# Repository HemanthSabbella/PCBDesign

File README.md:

# Hardware designs

- **EMI_sensing_board:** Design and Fabrication of EMI sensing board using a current transformer with a
low noise amplifier.
- **Constant Current LED Driver Board:** Design and Fabrication of constant current LED board for testing
portable spectrometer.
- **IIITDuino:** Design of in-home version of Arduino for IIIT-D.
- **Breakout Boards and custom made libraries:** Mux - ADG736, ADG719, LEDs - 1316, L424, LHT674,
OSI-330 series, VSMB2020.

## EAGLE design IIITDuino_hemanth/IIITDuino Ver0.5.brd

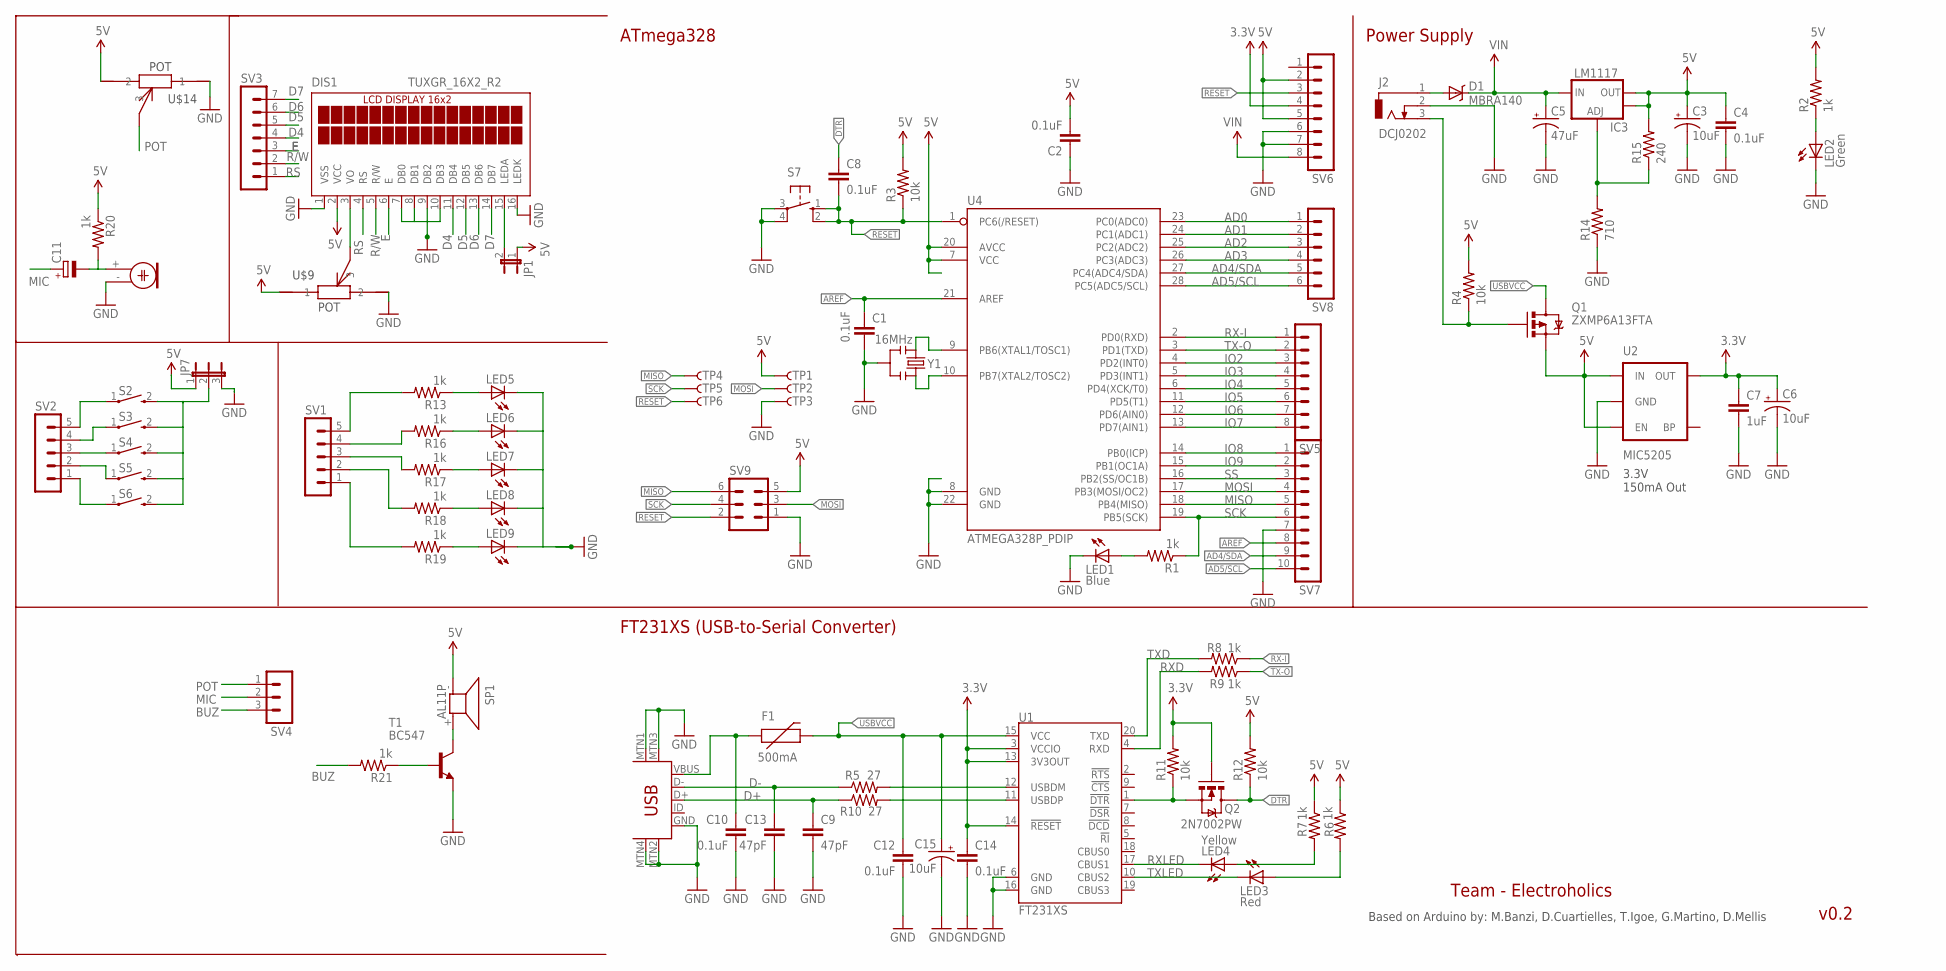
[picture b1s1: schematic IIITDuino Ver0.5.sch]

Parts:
C1, C2, C4, C8, C10, C12, C14: 0.1uF; 0603-CAP
C3, C6, C15: 10uF; EIA3216
C5: 47uF; PANASONIC_D
C7: 1uF; 0603-CAP
C9, C13: 47pF; 0603-CAP
C11: CPOL-EUE2.5-5; E2,5-5
D1: MBRA140; SMA-DIODE
DIS1: TUXGR_16X2_R2; LCD_16X2_PAC
F1: 500mA; PTC-1206
IC3: LM1117; SOT223-ALT1
J2: DCJ0202
JP1: JP1E; JP1
JP7: JP2E; JP2
LED1: Blue; LED-1206-NO_SILK
LED2: Green; LED-1206-NO_SILK
LED3: Red; LED-1206-NO_SILK
LED4: Yellow; LED-1206-NO_SILK
LED5, LED6, LED7, LED8, LED9: LEDCHIP-LED0805; CHIP-LED0805
M1: ELECTRET_MICROPHON-TOM-1545P-R; TOM-1545P-R
Q1: ZXMP6A13FTA; SOT23-3
Q2: 2N7002PW; SOT323
R1, R2, R6, R7, R8, R9, R13, R16, R17, R18, R19, R20, R21: 1k; 0603-RES
R3, R4, R11, R12: 10k; 0603-RES
R5, R10: 27; 0603-RES
R14: 710; 0603-RES
R15: 240; 0603-RES
S2, S3, S4, S5, S6, S7: 10-XX; B3F-10XX
SP1: AL11P
SV1, SV2: MA05-1
SV3: MA07-1
SV4: MA03-1
SV5, SV6: MA08-1
SV7: MA10-1
SV8: MA06-1
SV9: MA03-2
T1: BC547; TO92
TP1, TP2, TP3, TP4, TP5, TP6: TP-3x5; PAD.03X.05
U1: FT231XS; SSOP20_L
U2: MIC5205; SOT23-5
U4: ATMEGA328P_PDIP; DIL28-3
U$9, U$14: POT; CA9V
U$13: USB-MINIB-5PIN; USB-MINIB
Y1: 16MHz; RESONATOR-SMD

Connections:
3.3V: C6.A (+), C7.1, C14.1, Q2.1 (G), R11.2, SV6.4, U1.3 (VCCIO), U1.13 (3V3OUT), U1.14 (!RESET), U2.5 (OUT)
5V: C2.2, C3.A (+), C4.1, DIS1.2 (VCC), IC3.2 (OUT), IC3.4 (OUT), JP1.1, Q1.2 (S), R2.2, R3.2, R4.2, R6.1, R7.1, R12.2, R15.2, R20.1, SP1.- (1), SV6.2, SV6.5, SV9.5, TP1.P$1, U2.1 (IN), U2.3 (EN), U4.7 (VCC), U4.20 (AVCC), U$9.A (1), U$14.K (2)
AD0: SV8.1, U4.23 (PC0(ADC0))
AD1: SV8.2, U4.24 (PC1(ADC1))
AD2: SV8.3, U4.25 (PC2(ADC2))
AD3: SV8.4, U4.26 (PC3(ADC3))
AD4/SDA: SV7.9, SV8.5, U4.27 (PC4(ADC4/SDA))
AD5/SCL: SV7.10, SV8.6, U4.28 (PC5(ADC5/SCL))
AREF: C1.1, SV7.8, U4.21 (AREF)
BUZ: R21.2, SV4.3
D4: DIS1.11 (DB4), SV3.4
D5: DIS1.12 (DB5), SV3.5
D6: DIS1.13 (DB6), SV3.6
D7: DIS1.14 (DB7), SV3.7
D+: C9.1, R10.1, U$13.D+
D-: C13.1, R5.1, U$13.D-
DTR: C8.1, Q2.3 (D), R12.1
E: DIS1.6 (E), SV3.3
GND: C1.2, C2.1, C3.C (-), C4.2, C5.-, C6.C (-), C7.2, C9.2, C10.2, C12.2, C13.2, C14.2, C15.C (-), DIS1.1 (VSS), DIS1.7 (DB0), DIS1.8 (DB1), DIS1.9 (DB2), DIS1.10 (DB3), DIS1.16 (LEDK), J2.2, LED1.C, LED2.C, LED5.C, LED6.C, LED7.C, LED8.C, LED9.C, M1.- (2), R14.1, S7.3, S7.4 (P1), SV6.6, SV6.7, SV7.7, SV9.1, T1.1 (E), TP3.P$1, U1.6 (GND), U1.16 (GND), U2.2 (GND), U4.8 (GND), U4.22 (GND), U$9.K (2), U$13.GND, U$13.MTN1 (MTN2), U$13.MTN2 (MTN3), U$13.MTN3 (MTN1), U$13.MTN4, U$14.A (1), Y1.2
INSERT: J2.3, Q1.1 (G), R4.1
IO2: SV5.3, U4.4 (PD2(INT0))
IO3: SV5.4, U4.5 (PD3(INT1))
IO4: SV5.5, U4.6 (PD4(XCK/T0))
IO5: SV5.6, U4.11 (PD5(T1))
IO6: SV5.7, U4.12 (PD6(AIN0))
IO7: SV5.8, U4.13 (PD7(AIN1))
IO8: SV7.1, U4.14 (PB0(ICP))
IO9: SV7.2, U4.15 (PB1(OC1A))
MIC: C11.+, SV4.2
MISO: SV7.5, SV9.6, TP4.P$1, U4.18 (PB4(MISO))
MOSI: SV7.4, SV9.3, TP2.P$1, U4.17 (PB3(MOSI/OC2))
unnamed: LED1.A, R1.2
unnamed: LED2.A, R2.1
unnamed: U4.9 (PB6(XTAL1/TOSC1)), Y1.1
unnamed: U4.10 (PB7(XTAL2/TOSC2)), Y1.3
unnamed: DIS1.3 (VO), U$9.S (3)
unnamed: R5.2, U1.12 (USBDM)
unnamed: R10.2, U1.11 (USBDP)
unnamed: LED3.A, R6.2
unnamed: LED4.A, R7.2
unnamed: Q2.2 (S), R11.1, U1.1 (!DTR)
unnamed: IC3.1 (ADJ), R14.2, R15.1
unnamed: DIS1.15 (LEDA), JP1.2
unnamed: S2.1, SV2.5
unnamed: LED5.A, R13.1
unnamed: LED6.A, R16.1
unnamed: LED7.A, R17.1
unnamed: LED8.A, R18.1
unnamed: LED9.A, R19.1
unnamed: R13.2, SV1.5
unnamed: R16.2, SV1.4
unnamed: R17.2, SV1.3
unnamed: R18.2, SV1.2
unnamed: R19.2, SV1.1
unnamed: S3.1, SV2.4
unnamed: S4.1, SV2.3
unnamed: S5.1, SV2.2
unnamed: S6.1, SV2.1
unnamed: JP7.2, S2.2 (S), S3.2 (S), S4.2 (S), S5.2 (S), S6.2 (S)
unnamed: SP1.+ (2), T1.3 (C)
unnamed: C11.-, M1.+ (1), R20.2
unnamed: R21.1, T1.2 (B)
POT: SV4.1, U$14.S (3)
PWRIN: D1.A, J2.1
R/W: DIS1.5 (R/W), SV3.2
RESET: C8.2, R3.1, S7.1 (S), S7.2 (S1), SV6.3, SV9.2, TP6.P$1, U4.1 (PC6(/RESET))
RS: DIS1.4 (RS), SV3.1
RX-I: R8.1, SV5.1, U4.2 (PD0(RXD))
RXD: R9.2, U1.4 (RXD)
RXLED: LED4.C, U1.17 (CBUS1)
SCK: R1.1, SV7.6, SV9.4, TP5.P$1, U4.19 (PB5(SCK))
SS: SV7.3, U4.16 (PB2(SS/OC1B))
TX-O: R9.1, SV5.2, U4.3 (PD1(TXD))
TXD: R8.2, U1.20 (TXD)
TXLED: LED3.C, U1.10 (CBUS2)
USBVCC: C12.1, C15.A (+), F1.2, Q1.3 (D), U1.15 (VCC)
VIN: C5.+, D1.C, IC3.3 (IN), SV6.8
VUSB: C10.1, F1.1, U$13.VBUS

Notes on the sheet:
Power Supply
ATmega328
FT231XS (USB-to-Serial Converter)
Based on Arduino by: M.Banzi, D.Cuartielles, T.Igoe, G.Martino, D.Mellis
3.3V 150mA Out
Team - Electroholics
v0.2

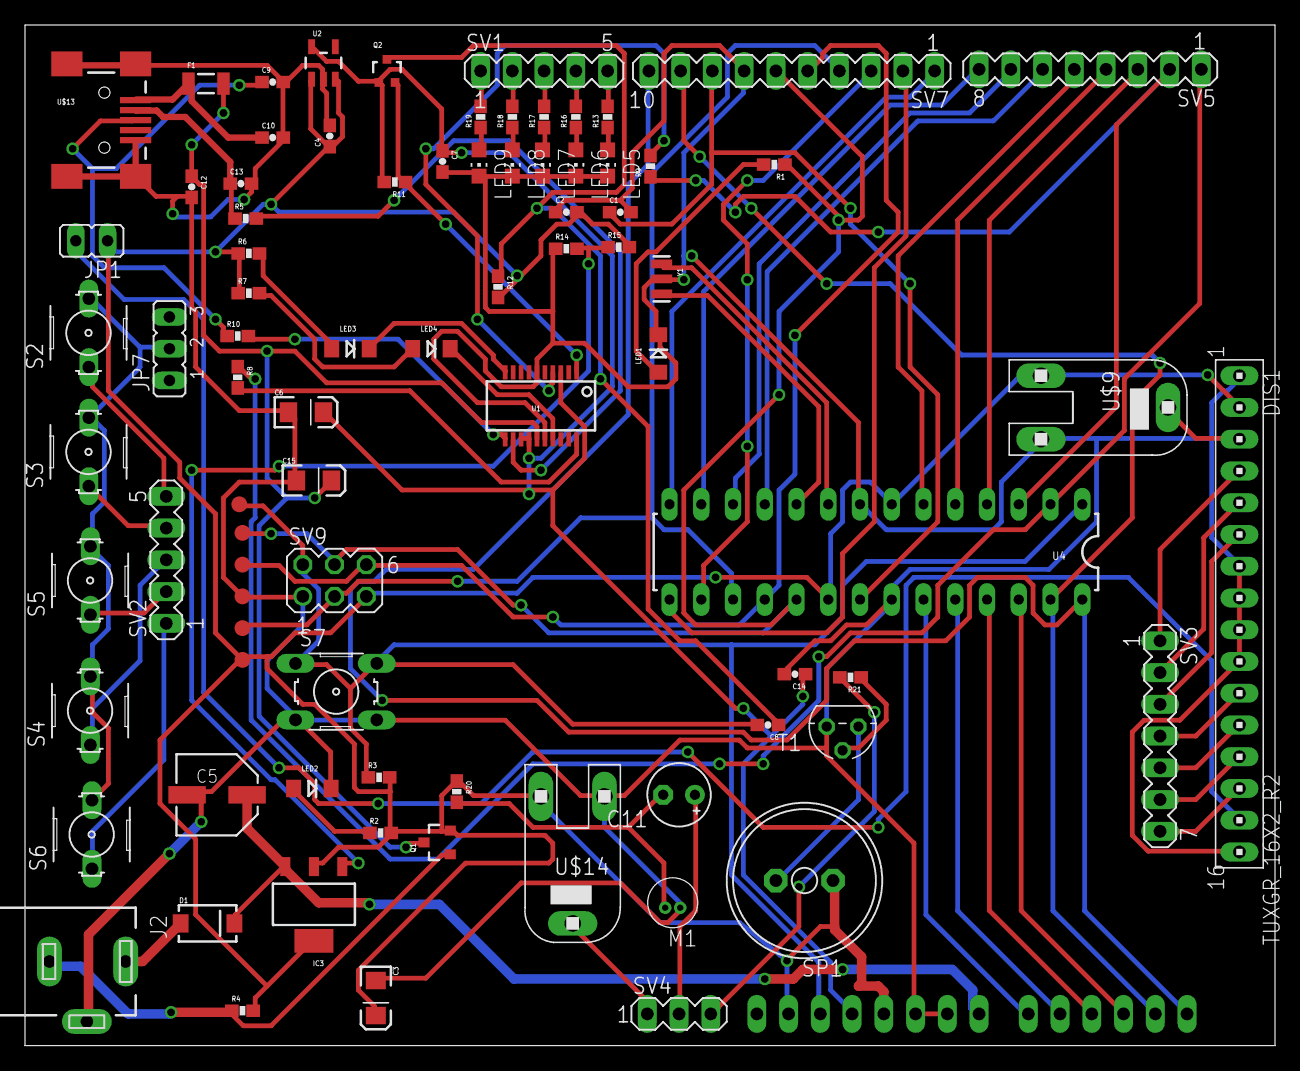
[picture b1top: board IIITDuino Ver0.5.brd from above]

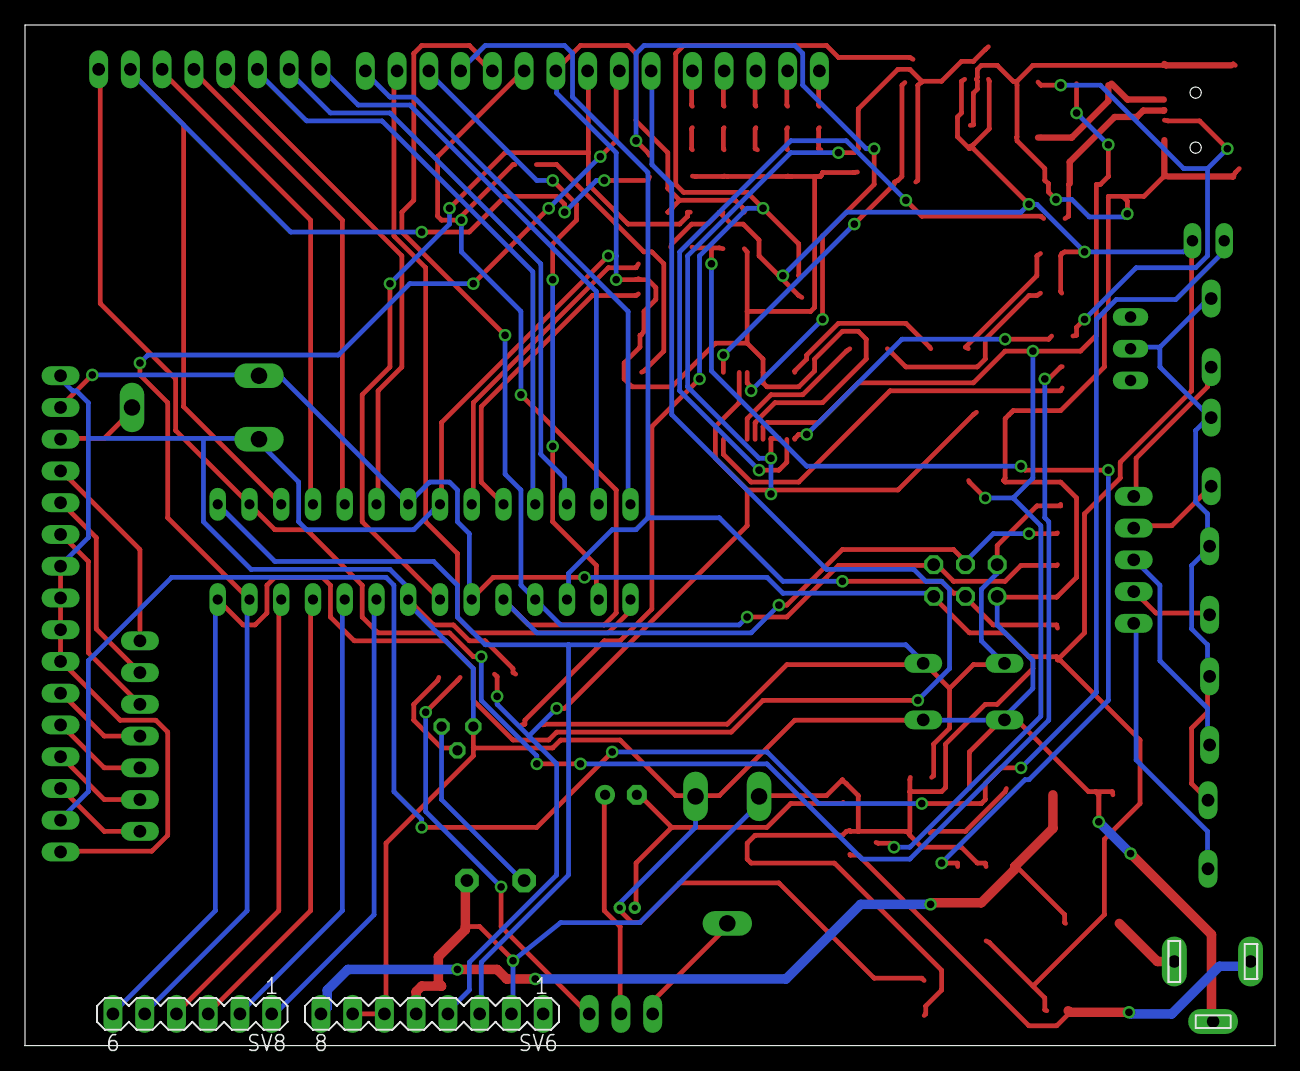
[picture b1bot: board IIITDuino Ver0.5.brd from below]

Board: 2 copper layers, 99.9 x 81.5 mm, 85 parts (2 on the bottom side), 78 nets.

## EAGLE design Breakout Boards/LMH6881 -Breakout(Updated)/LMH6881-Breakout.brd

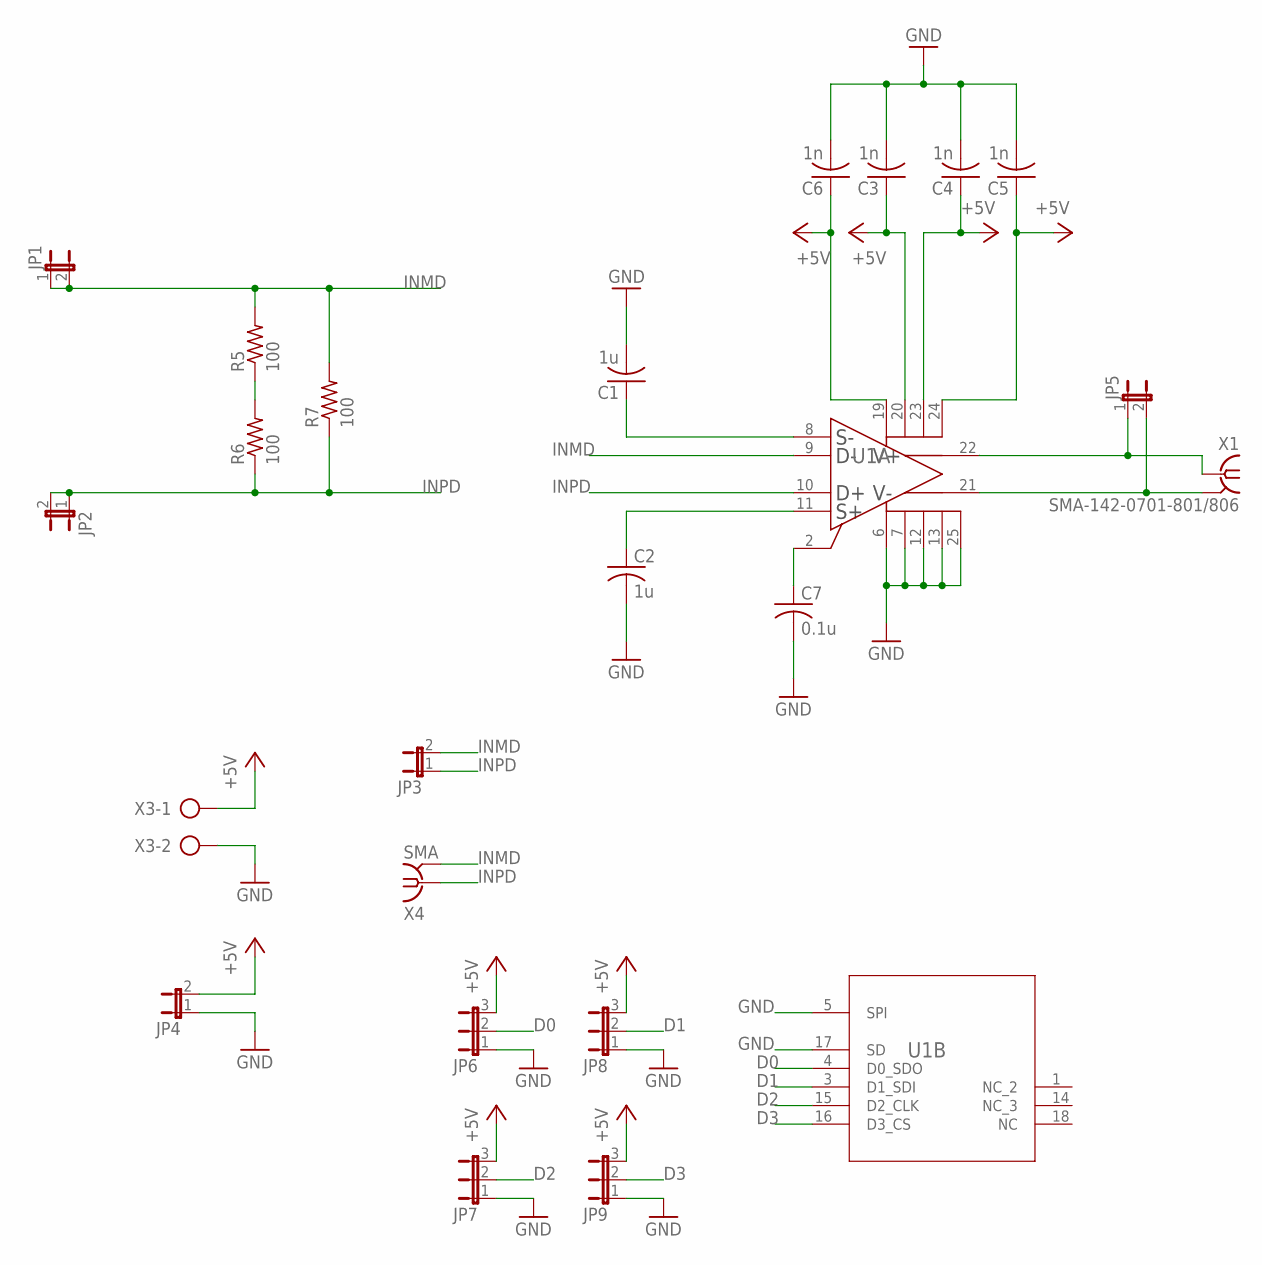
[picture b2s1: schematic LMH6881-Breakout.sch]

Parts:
C1, C2: 1u; C0805
C3, C4, C5, C6: 1n; C0805
C7: 0.1u; C0805
JP1, JP2, JP3, JP4, JP5: JP1E; JP1
JP6, JP7, JP8, JP9: JP2E; JP2
R5, R6, R7: 100; R0805
U1: LMH6881SQX/NOPB; RTW0024A
X1: SMA-142-0701-801/806; J502-ND-142-0701-801/806
X3: AK500/2
X4: SMA; J502-ND-142-0701-801/806

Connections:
+5V: C3.1, C4.1, C5.1, C6.1, JP4.2, JP6.3, JP7.3, JP8.3, JP9.3, U1.19 (VCC_2), U1.20 (VCC_3), U1.23 (VCC_4), U1.24 (VCC), X3.1
D0: JP6.2, U1.4 (D0_SDO)
D1: JP8.2, U1.3 (D1_SDI)
D2: JP7.2, U1.15 (D2_CLK)
D3: JP9.2, U1.16 (D3_CS)
GND: C1.2, C2.2, C3.2, C4.2, C5.2, C6.2, C7.2, JP4.1, JP6.1, JP7.1, JP8.1, JP9.1, U1.5 (SPI), U1.6 (GND_2), U1.7 (GND_3), U1.12 (GND_4), U1.13 (GND), U1.17 (SD), U1.25 (PAD), X3.2
INMD: JP1.1, JP1.2, JP3.2, R5.2, R7.2, U1.9 (INMD), X4.G@1 (2), X4.G@2 (2), X4.G@3 (2), X4.G@4 (2)
INPD: JP2.1, JP2.2, JP3.1, R6.1, R7.1, U1.10 (INPD), X4.1
unnamed: C7.1, U1.2 (OCM)
unnamed: C1.1, U1.8 (INMS)
unnamed: C2.1, U1.11 (INPS)
unnamed: JP5.1, U1.22 (OUTP), X1.1
unnamed: JP5.2, U1.21 (OUTM), X1.G@1 (2), X1.G@2 (2), X1.G@3 (2), X1.G@4 (2)
unnamed: R5.1, R6.2

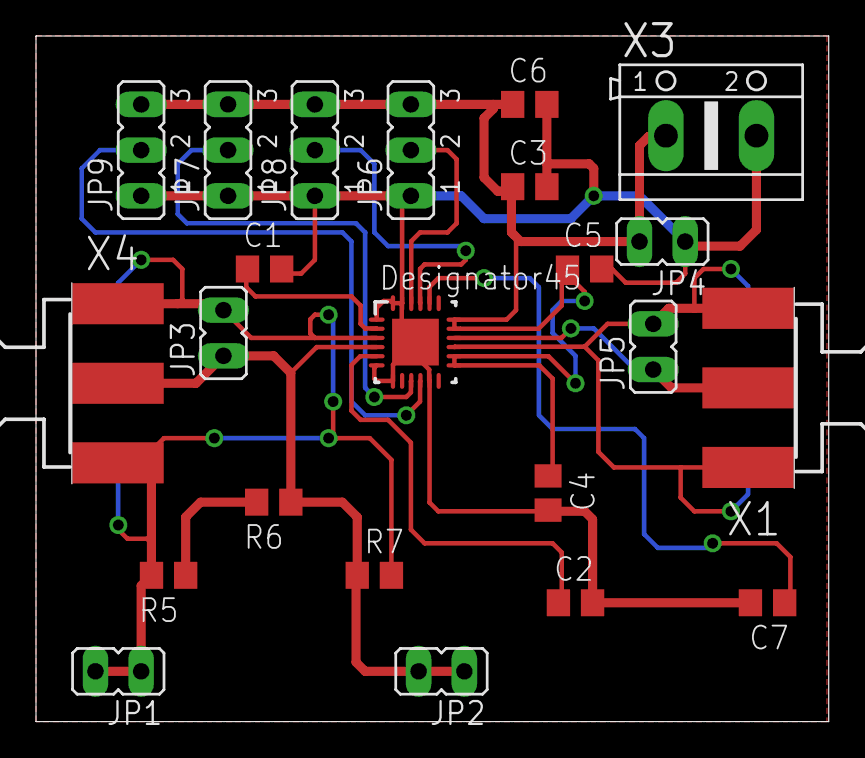
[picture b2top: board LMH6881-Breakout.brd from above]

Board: 2 copper layers, 44.0 x 38.1 mm, 23 parts (0 on the bottom side), 14 nets.

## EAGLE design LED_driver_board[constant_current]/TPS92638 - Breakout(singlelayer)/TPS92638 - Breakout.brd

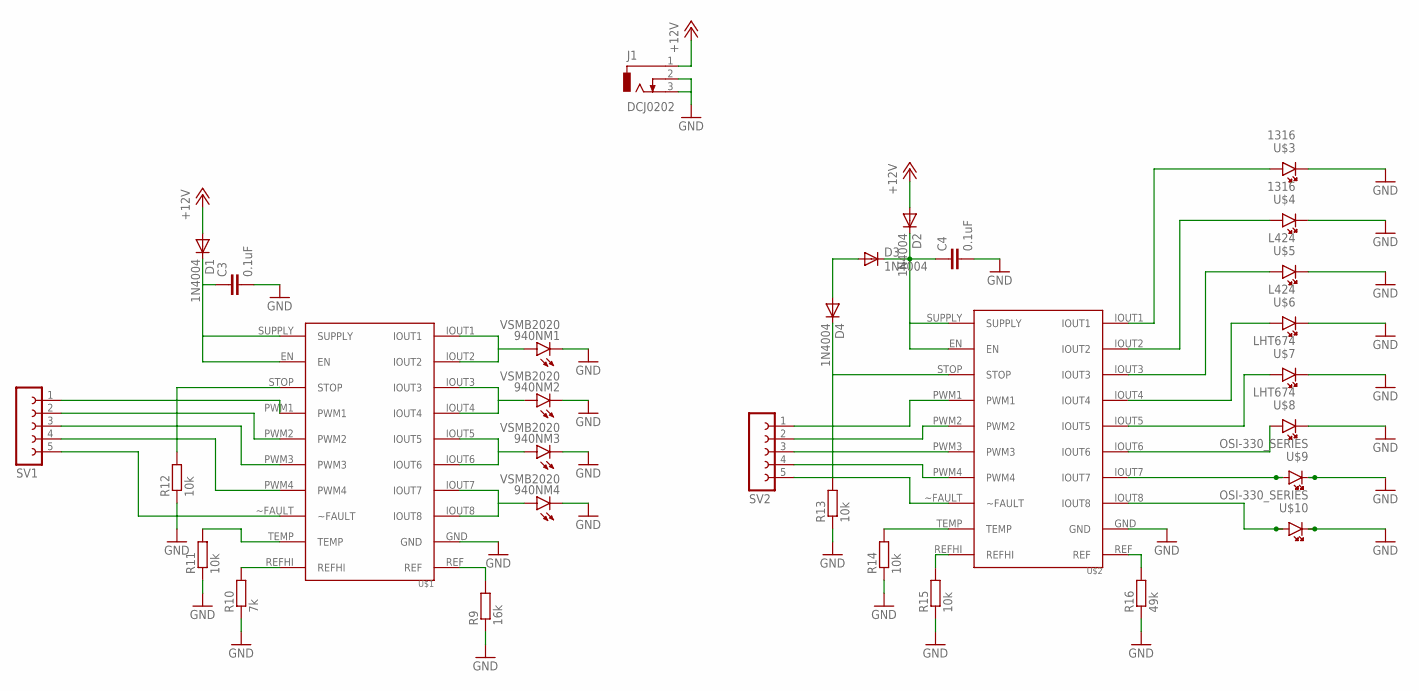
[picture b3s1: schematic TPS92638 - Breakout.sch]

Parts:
940NM1, 940NM2, 940NM3, 940NM4: VSMB2020; GULLWING-2.3MM
C3, C4: 0.1uF; C025-024X044
D1, D2, D3, D4: 1N4004; DO41-10
J1: DCJ0202
R9: 16k; 0204/7
R10: 7k; 0204/7
R11, R12, R13, R14, R15: 10k; 0204/7
R16: 49k; 0204/7
SV1, SV2: FE05-1
U$1, U$2: TPS92638
U$3, U$4: 1316
U$5, U$6: L424
U$7, U$8: LHT674
U$9, U$10: OSI-330_SERIES

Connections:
+12V: D1.A, D2.A, J1.1
GND: 940NM1.P$2 (C), 940NM2.P$2 (C), 940NM3.P$2 (C), 940NM4.P$2 (C), C3.2, C4.2, J1.2, J1.3, R9.1, R10.1, R11.1, R12.1, R13.1, R14.1, R15.1, R16.1, U$1.GND, U$2.GND, U$3.CATHODE, U$4.CATHODE, U$5.CATHODE, U$6.CATHODE, U$7.CATHODE, U$8.CATHODE, U$9.CATHODE, U$10.CATHODE
unnamed: SV1.1, U$1.PWM1
unnamed: SV1.2, U$1.PWM2
unnamed: SV1.3, U$1.PWM3
unnamed: SV1.4, U$1.PWM4
unnamed: R12.2, U$1.STOP
unnamed: SV2.1, U$2.PWM1
unnamed: SV2.2, U$2.PWM2
unnamed: SV2.3, U$2.PWM3
unnamed: SV2.4, U$2.PWM4
unnamed: D4.C, R13.2, U$2.STOP
unnamed: R10.2, U$1.REFHI
unnamed: R11.2, U$1.TEMP
unnamed: R9.2, U$1.REF
unnamed: R14.2, U$2.TEMP
unnamed: R15.2, U$2.REFHI
unnamed: R16.2, U$2.REF
unnamed: C3.1, D1.C, U$1.EN, U$1.SUPPLY
unnamed: C4.1, D2.C, D3.C, U$2.EN, U$2.SUPPLY
unnamed: 940NM1.P$1 (A), U$1.IOUT1, U$1.IOUT2
unnamed: 940NM2.P$1 (A), U$1.IOUT3, U$1.IOUT4
unnamed: U$2.IOUT1, U$3.ANODE
unnamed: 940NM3.P$1 (A), U$1.IOUT5, U$1.IOUT6
unnamed: 940NM4.P$1 (A), U$1.IOUT7, U$1.IOUT8
unnamed: U$2.IOUT2, U$4.ANODE
unnamed: U$2.IOUT3, U$5.ANODE
unnamed: U$2.IOUT4, U$6.ANODE
unnamed: U$2.IOUT5, U$7.ANODE
unnamed: U$2.IOUT6, U$8.ANODE
unnamed: U$2.IOUT7, U$9.ANODE
unnamed: U$2.IOUT8, U$10.ANODE
unnamed: SV1.5, U$1.~FAULT
unnamed: SV2.5, U$2.~FAULT
unnamed: D3.A, D4.A

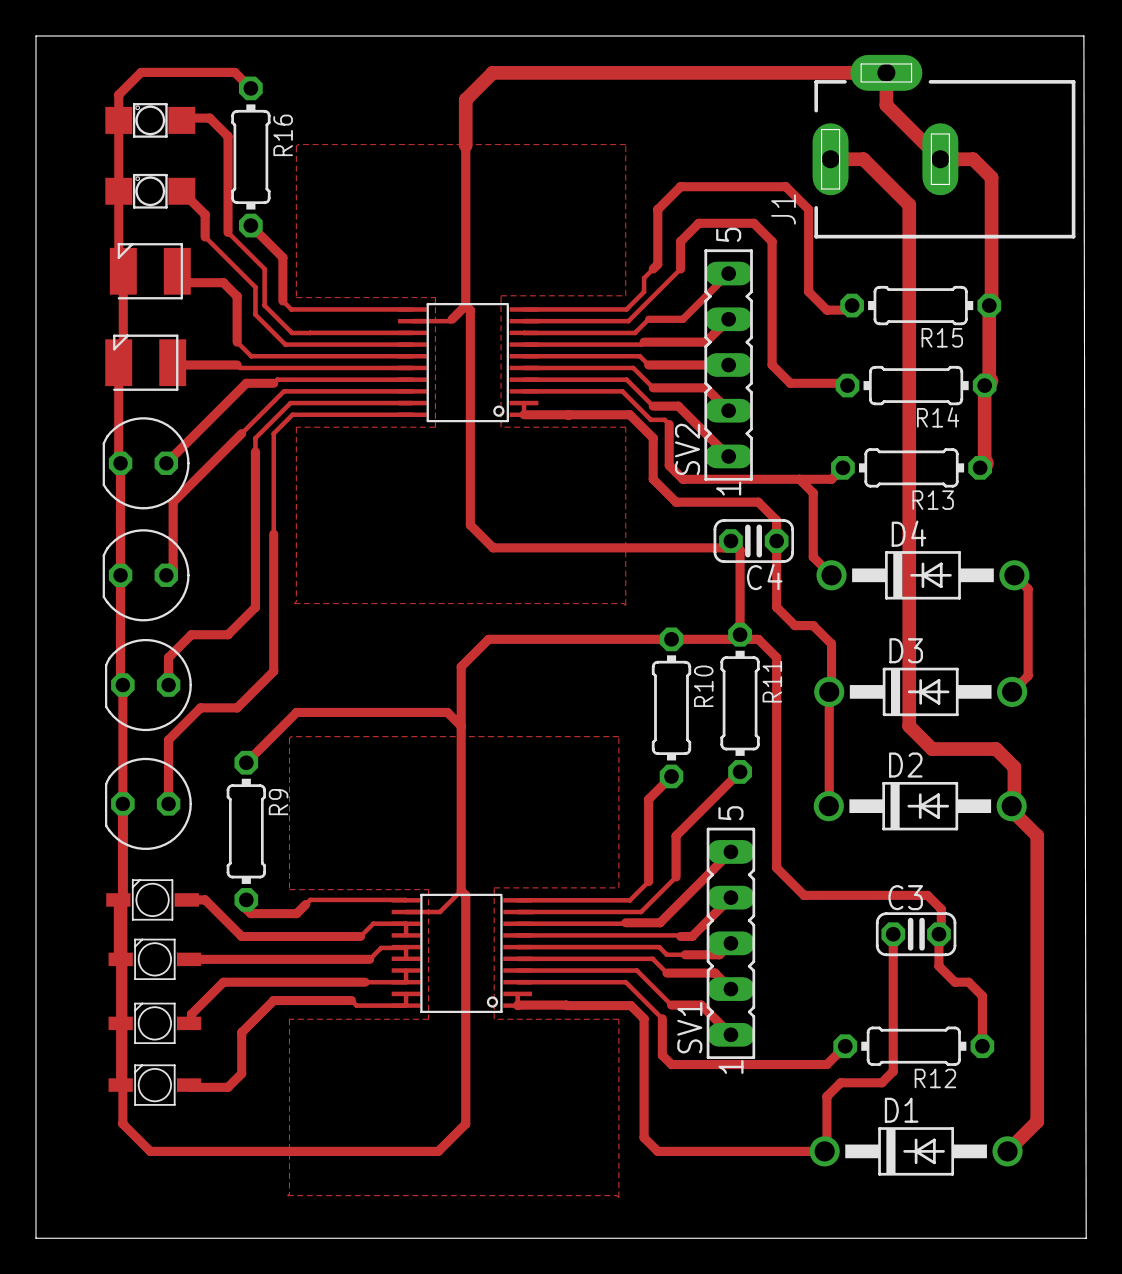
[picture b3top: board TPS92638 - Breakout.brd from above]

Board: 2 copper layers, 58.3 x 66.8 mm, 31 parts (0 on the bottom side), 35 nets.

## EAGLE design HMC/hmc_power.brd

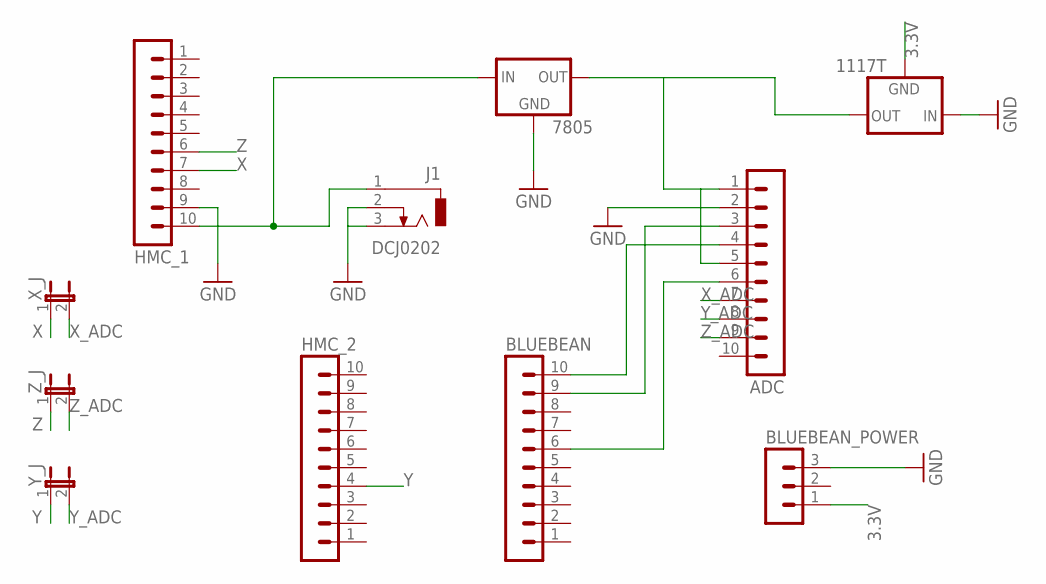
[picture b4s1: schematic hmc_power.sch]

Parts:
1117T, 7805: 78XXL
ADC: MA10-1
BLUEBEAN: MA10-1
BLUEBEAN_POWER: MA03-1
HMC_1, HMC_2: MA10-1
J1: DCJ0202
X_J: JP1E; JP1
Y_J: JP1E; JP1
Z_J: JP1E; JP1

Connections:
3.3V: 1117T.GND, BLUEBEAN_POWER.1
A1: 7805.IN, HMC_1.10, J1.1
GND: 1117T.IN, 7805.GND, ADC.2, BLUEBEAN_POWER.3, HMC_1.9, J1.2, J1.3
unnamed: 1117T.OUT, 7805.OUT, ADC.1, ADC.5
unnamed: ADC.3, BLUEBEAN.9
unnamed: ADC.4, BLUEBEAN.10
unnamed: ADC.6, BLUEBEAN.6
X: HMC_1.7, X_J.1
X_ADC: ADC.7, X_J.2
Y: HMC_2.4, Y_J.1
Y_ADC: ADC.8, Y_J.2
Z: HMC_1.6, Z_J.1
Z_ADC: ADC.9, Z_J.2

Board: 2 copper layers, 11 parts (0 on the bottom side), 13 nets, no tracks yet.

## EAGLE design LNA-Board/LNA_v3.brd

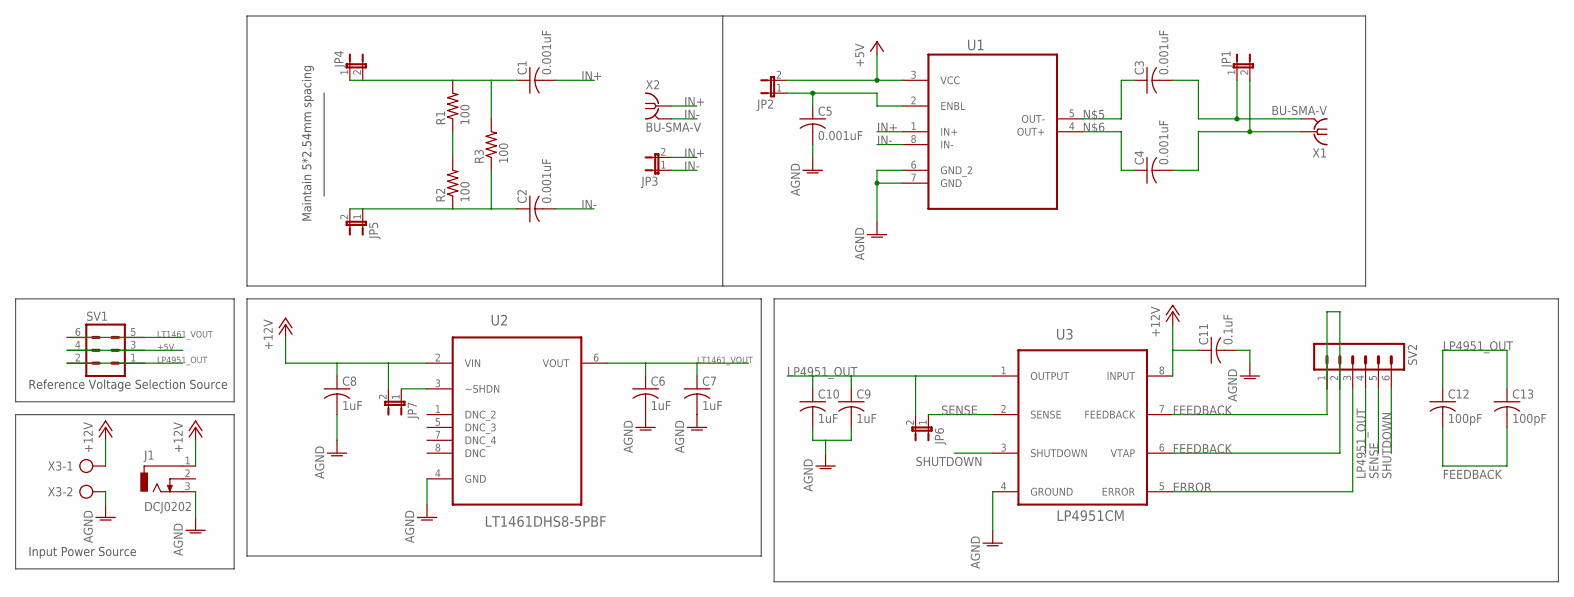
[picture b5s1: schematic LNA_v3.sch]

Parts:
C1, C2, C3, C4, C5: 0.001uF; C0805
C6, C7, C8, C9, C10: 1uF; C0805
C11: 0.1uF; C0805
C12, C13: 100pF; C0805
J1: DCJ0202
JP1, JP2, JP3, JP4, JP5, JP6, JP7: JP1E; JP1
R1, R2, R3: 100; R0805
SV1: MA03-2
SV2: MA06-1
U1: AD8350ARMZ20; SOP65P490X110-8N
U2: LT1461DHS8-5PBF; SOIC127P600X175-8N
U3: LP4951CM; SOIC127P600X175-8N
X1, X2: BU-SMA-V
X3: AK500/2

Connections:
+5V: JP2.2, SV1.3, SV1.4, U1.3 (VCC)
+12V: C8.1, C11.1, J1.1, JP7.2, U2.2 (VIN), U3.8 (INPUT), X3.1
AGND: C5.2, C6.2, C7.2, C8.2, C9.2, C10.2, C11.2, J1.3, U1.6 (GND_2), U1.7 (GND), U2.4 (GND), U3.4 (GROUND), X3.2
ERROR: SV2.3, U3.5 (ERROR)
FEEDBACK: C12.2, C13.2, SV2.1, SV2.2, U3.6 (VTAP), U3.7 (FEEDBACK)
IN+: C1.2, JP3.2, U1.1 (IN+), X2.1
IN-: C2.2, JP3.1, U1.8 (IN-), X2.2, X2.3 (2), X2.4 (2), X2.5 (2)
LP4951_OUT: C9.1, C10.1, C12.1, C13.1, JP6.2, SV1.1, SV1.2, SV2.4, U3.1 (OUTPUT)
LT1461_VOUT: C6.1, C7.1, SV1.5, SV1.6, U2.6 (VOUT)
unnamed: C1.1, JP4.1, JP4.2, R1.2, R3.2
unnamed: R1.1, R2.2
unnamed: C5.1, JP2.1, U1.2 (ENBL)
unnamed: C2.1, JP5.1, JP5.2, R2.1, R3.1
unnamed: C3.1, U1.5 (OUT-)
unnamed: C4.1, U1.4 (OUT+)
unnamed: JP7.1, U2.3 (~SHDN)
OUT+: C4.2, JP1.2, X1.1
OUT-: C3.2, JP1.1, X1.2, X1.3 (2), X1.4 (2), X1.5 (2)
SENSE: JP6.1, SV2.5, U3.2 (SENSE)
SHUTDOWN: SV2.6, U3.3 (SHUTDOWN)

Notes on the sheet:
Maintain 5*2.54mm spacing
Reference Voltage Selection Source
Input Power Source

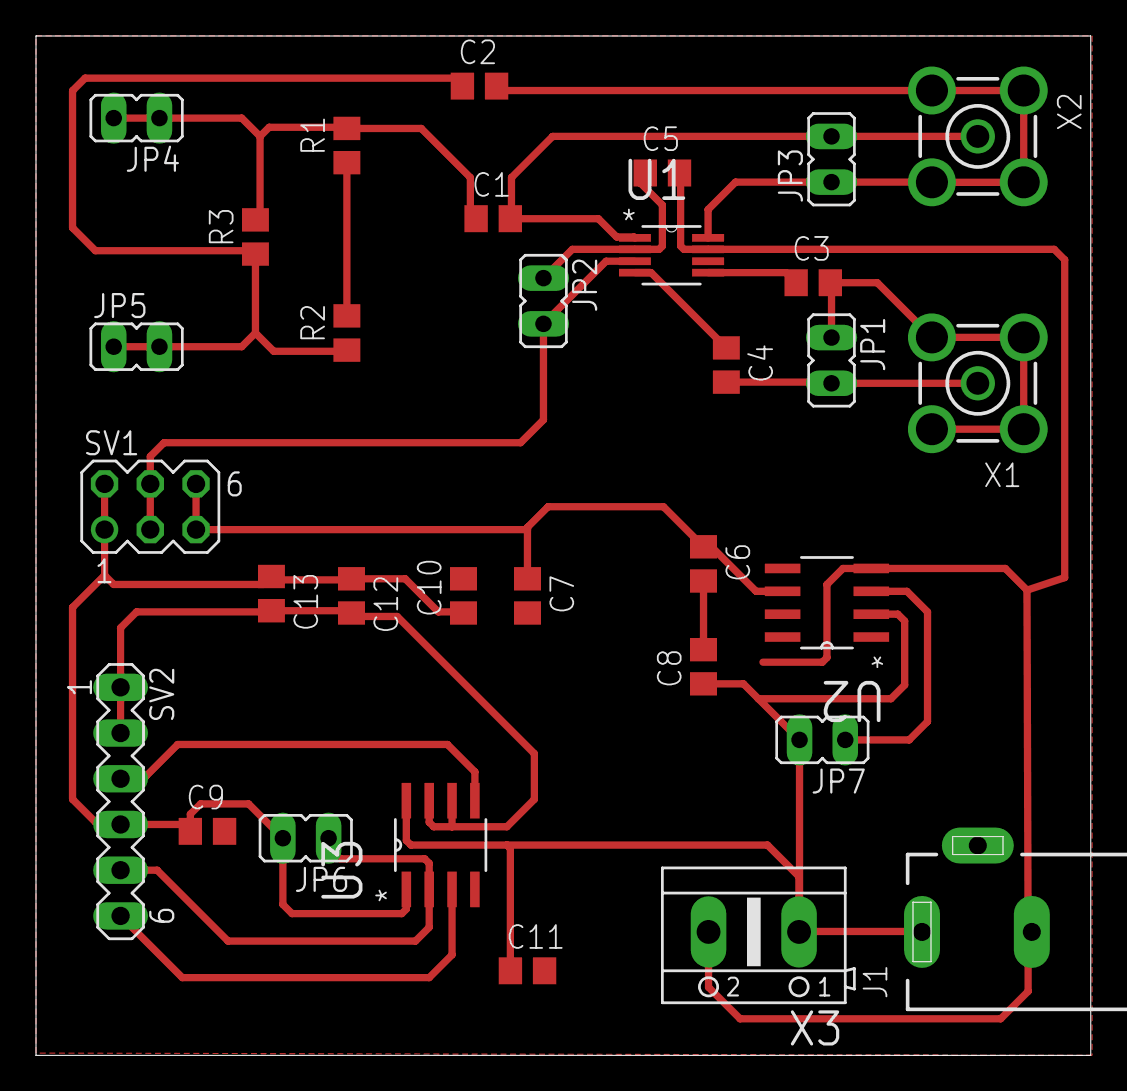
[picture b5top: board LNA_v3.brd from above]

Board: 2 copper layers, 58.6 x 56.6 mm, 32 parts (0 on the bottom side), 20 nets.

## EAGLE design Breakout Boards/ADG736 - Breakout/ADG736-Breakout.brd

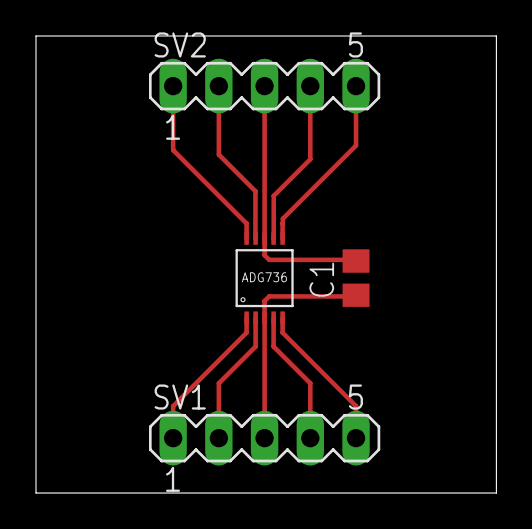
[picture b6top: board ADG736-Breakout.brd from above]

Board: 2 copper layers, 25.6 x 25.4 mm, 4 parts (0 on the bottom side), 10 nets.

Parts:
C1: 0.1uF; C0805
SV1, SV2: MA05-1
U$1: ADG736

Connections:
D1_: SV2.1, U$1.10
D2_: SV2.5, U$1.6
GND: C1.1, SV1.3, U$1.3
IN1_: SV1.1, U$1.1
IN2_: SV1.5, U$1.5
S1A_: SV1.2, U$1.2
S1B_: SV2.2, U$1.9
S2A_: SV1.4, U$1.4
S2B_: SV2.4, U$1.7
VDD: C1.2, SV2.3, U$1.8

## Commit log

2018-08-01 Designs added
2021-01-12 Seggregated the boards

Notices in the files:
parts and their libraries:
SparkFun-Capacitors: Licensing: CC v3.0 Share-Alike You are welcome to use this library for commercial purposes.
SparkFun-Aesthetics: Released under the Creative Commons Attribution Share-Alike 3.0 License
SparkFun-Aesthetics: http://creativecommons.org/licenses/by-sa/3.0
